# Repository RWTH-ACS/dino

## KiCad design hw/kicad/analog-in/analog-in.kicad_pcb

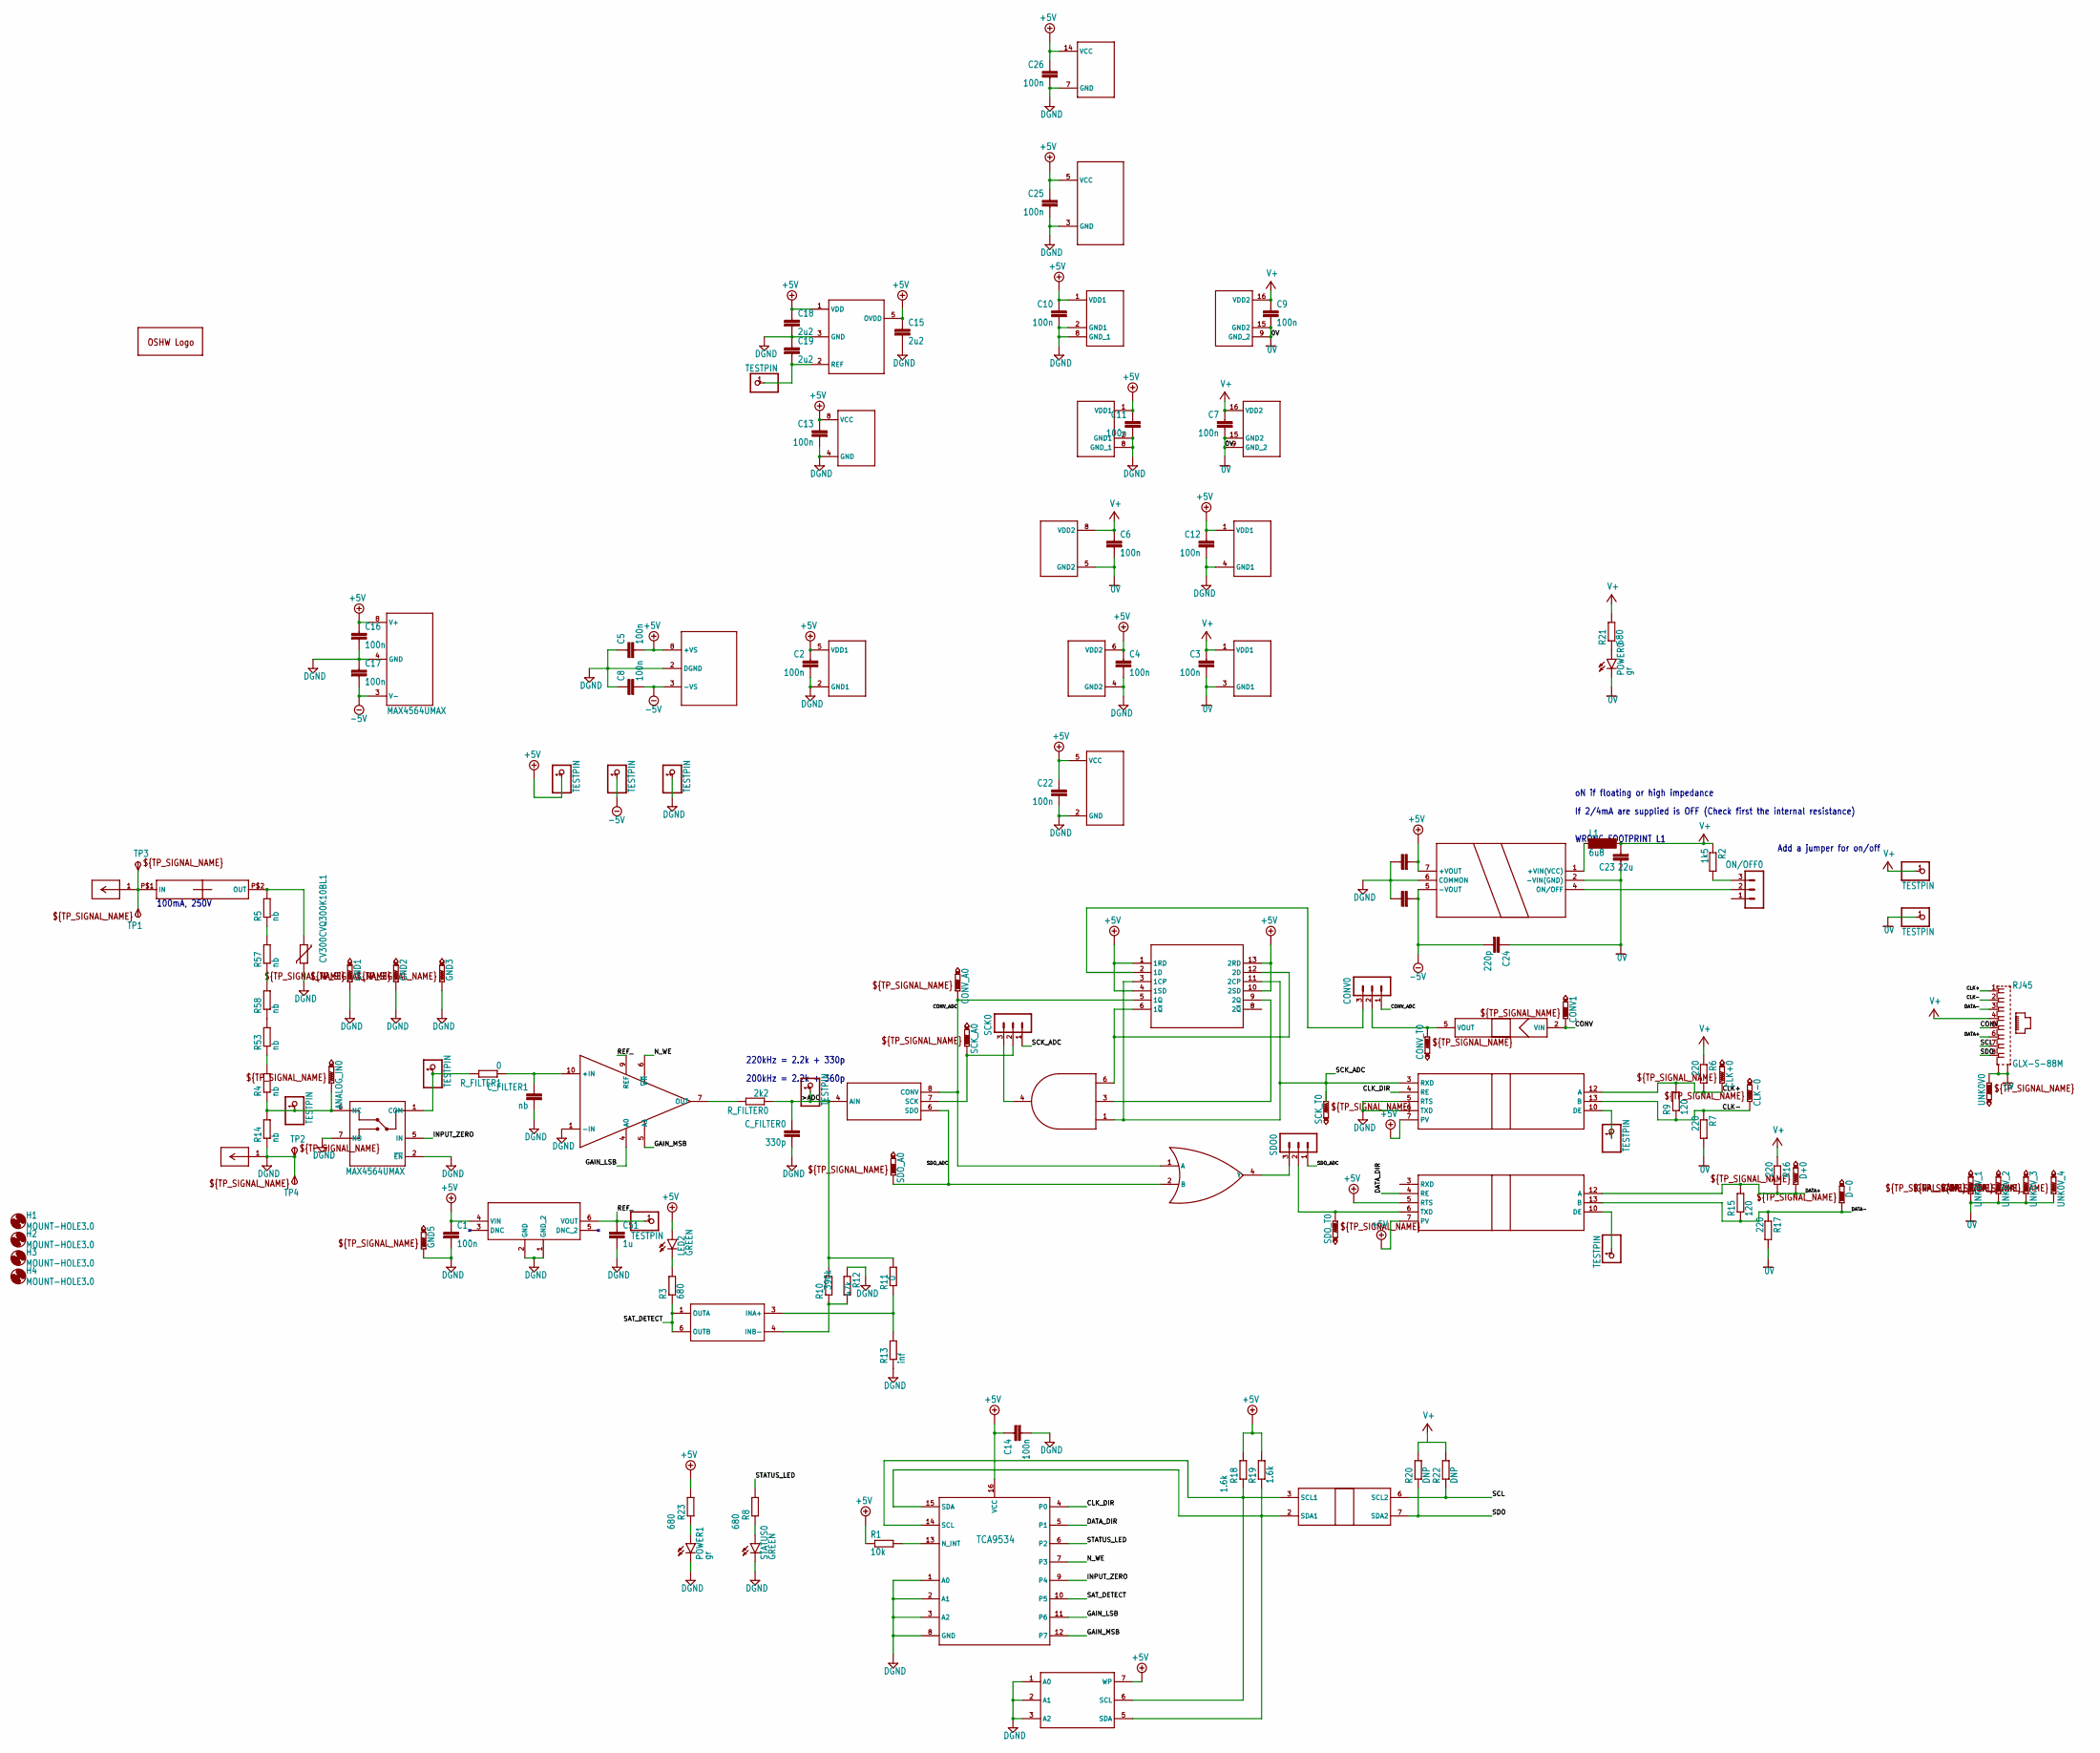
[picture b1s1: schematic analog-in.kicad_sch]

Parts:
+5V0: TESTPIN; 1X01
-5V0: TESTPIN; 1X01
ADC_0: LTC2314-14; TSOT-23_TS8_LIT; DIGIKEY LTC2314ITS8-14#TRMPBFT-ND
ADC_IN0: TESTPIN; 1X01
ADC_REF0: TESTPIN; 1X01
ANALOG_IN0: PTR1B1,27; B1,27
A_IN0: TESTPIN; 1X01
C1: 100n; C0805; DIGIKEY 478-7962-1-ND
C2, C3, C4, C5, C6, C7, C8, C9, C10, C11, C12, C13, C14, C16, C17, C20, C21, C22, C25, C26: 100n; C0805K; DIGIKEY 478-7962-1-ND
C15, C18, C19: 2u2; C0805K; DIGIKEY 1276-2954-2-ND
C23: 22u; C1206; DIGIKEY 399-17625-1-ND
C24: 220p; C1808; DIGIKEY 478-10448-2-ND
C51: 1u; C0805; DIGIKEY 1276-6471-1-ND
CLK+0: PTR1B1,27; B1,27
CLK-0: PTR1B1,27; B1,27
CONV0: MA03-1; DIGIKEY 732-5316-ND
CONV1: PTR1B1,27; B1,27
CONVERSION0: ADUM4120-1ARIZ; RI_6_1_ADI; DIGIKEY ADUM4120-1ARIZ-ND
CONV_A0: PTR1B1,27; B1,27
CONV_T0: PTR1B1,27; B1,27
C_FILTER0: 330p; C0805K; DIGIKEY 478-9885-1-ND
C_FILTER1: nb; C0805K; DIGIKEY 478-08055C121KAT2ACT-ND
D+0: PTR1B1,27; B1,27
D-0: PTR1B1,27; B1,27
DC-DC_CONVERTER0: TDN_3-1211WI; TDN3_TRP; MANUFACTURER_PART_NUMBER TDN 3-1221WISM; DIGIKEY TDN3-1221WISM-ND
DE_CLK0: TESTPIN; 1X01
DE_DATA0: TESTPIN; 1X01
DGND0: TESTPIN; 1X01
FILTER0: TESTPIN; 1X01
FLIP-FLOP0: 74HC74PW-Q100,118; TSSOP14_SOT402-1_NEX; DIGIKEY 1727-4083-1-ND
GND1, GND2, GND3, GND5: PTR1B1,27; B1,27
GND_4: TESTPIN; 1X01
GOLD_ORB_SM1: OSHWLOGOLOGO8MM; OSHW_8MM
H1, H2, H3, H4: MOUNT-HOLE3.0; 3,0
I2C0: ADUM1251WARZ; R_8_ADI; DIGIKEY ADUM1251ARZ-RL7TR-ND
INSTR_AMP0: AD8250ARMZ; RM_10_ADI; DIGIKEY AD8250ARMZ-R7TR-ND
L1: 6u8; SM-NE29; DIGIKEY 1951-1045-ND
LED2: GREEN; SML0805; DIGIKEY LTST-C170GKT
MINUS0: 23.3200-21; CONN_23.3200-21_SBI; DIGIKEY 501-73099-0-ND
MOV1: CV300CVQ300K10BL1; CVQ300K10
ON/OFF0: MA03-1; DIGIKEY 732-5316-ND
PLUS0: 23.3200-21; CONN_23.3200-21_SBI; DIGIKEY 501-73099-2-ND
POWER0, POWER1: gr; SML0805; DIGIKEY LTST-C170GKT
R1: 10k; R0805; DIGIKEY P10KDATR-ND
R2: 1k5; R0805; DIGIKEY P1.5KDATR-ND
R3, R21: 680; R0805; DIGIKEY A129747TR-ND
R4, R5, R53, R57, R58: nb; R1206; MOUSER check config
R6, R7, R16, R17: 220; R0805; DIGIKEY Y1624195R000Q9R-ND
R8, R23: 680; R0805
R9, R15: 120; R0805; DIGIKEY Y1629-120DTR-ND
R10: 390k; R0805; DIGIKEY 2019-RK73H2ATTD3903FTR-ND
R11: 0; R0805; DIGIKEY RMCF0805ZT0R00TR-ND
R12: 47k; R0805; DIGIKEY A130144TR-ND
R13: inf; R0805
R14: nb; R0805; MOUSER check config
R18, R19: 1.6k; R0805
R20, R22: DNP; R0805
REF0: LT6654AIS6-2.048TRMPBF; S_6_ADI; DIGIKEY 161-LT6654BHS6-2.048#WTRPBFTR-ND
REF_2.048: TESTPIN; 1X01
RJ45: GLX-S-88M; DIGIKEY 2092-GLX-S-88M-ND
ROHM_I2C0: BR24T1MF-3AM; BR24T1MFJ-3AM; DIGIKEY BR24T1MF-3AME2TR-ND
R_FILTER0: 2k2; R0805; DIGIKEY A106060TR-ND
R_FILTER1: 0; R0805; DIGIKEY P220DACT-ND
SATURATION_DETECT0: ADCMP670-1YUJZ-RL7; UJ_6_ADI; DIGIKEY ADCMP670-1YUJZ-RL7TR-ND
SCK0: MA03-1; DIGIKEY 732-5316-ND
SCK_A0: PTR1B1,27; B1,27
SCK_T0: PTR1B1,27; B1,27
SDO0: MA03-1; DIGIKEY 732-5316-ND
SDO_A0: PTR1B1,27; B1,27
SDO_T0: PTR1B1,27; B1,27
SERIAL_CLOCK0: ADM2486BRWZ-REEL; RW_16_ADI; DIGIKEY ADM2486BRWZ-REELTR-ND
SERIAL_DATA0: ADM2486BRWZ-REEL; RW_16_ADI; DIGIKEY ADM2486BRWZ-REELTR-ND
SN74LVC1G32: SN74LVC1G32DCKTDCK5-M; DCK5-M
STATUS0: GREEN; CHIPLED_0805; DIGIKEY LTST-C170GKT
TP1, TP2, TP3, TP4: TPSTP20SQ; TP20SQ
U$1: 0508.500MXEP; DIGIKEY 283-4458-1-ND
U$2: TCA9534; TSSOP16L
U$20: MAX4564UMAX; UMAX8; DIGIKEY MAX4564EUA+TR-ND
UNK0V0, UNK0V_1, UNK0V_2, UNK0V_3, UNK0V_4: PTR1B1,27; B1,27
UNK74LVC1G11: SN74LVC1G11DBVRDBV0006A_L; DBV0006A_L
VCC0: TESTPIN; 1X01

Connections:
0V: C3.2, C6.2, C7.2, C9.2, C23.1, C24.1, CONVERSION0.3 (GND1), DC-DC_CONVERTER0.2 (-VIN(GND)), DGND0.1, I2C0.5 (GND2), POWER0.C, R7.2, R17.2, RJ45.S1, RJ45.S2, SERIAL_CLOCK0.9 (GND_2), SERIAL_CLOCK0.15 (GND2), SERIAL_DATA0.9 (GND_2), SERIAL_DATA0.15 (GND2), UNK0V0.TP, UNK0V_1.TP, UNK0V_2.TP, UNK0V_3.TP, UNK0V_4.TP
+5V: +5V0.1, ADC_0.1 (VDD), ADC_0.5 (OVDD), C1.1, C2.1, C4.1, C5.2, C10.1, C11.1, C12.1, C13.1, C14.1, C15.1, C16.1, C18.1, C20.2, C22.1, C25.1, C26.1, CONVERSION0.6 (VDD2), DC-DC_CONVERTER0.7 (+VOUT), FLIP-FLOP0.1 (1RD), FLIP-FLOP0.4 (1SD), FLIP-FLOP0.10 (2SD), FLIP-FLOP0.13 (2RD), FLIP-FLOP0.14 (VCC), I2C0.1 (VDD1), INSTR_AMP0.8 (+VS), LED2.A, R1.1, R18.2, R19.2, R23.2, REF0.4 (VIN), ROHM_I2C0.7 (WP), ROHM_I2C0.8 (VCC), SATURATION_DETECT0.5 (VDD1), SERIAL_CLOCK0.1 (VDD1), SERIAL_CLOCK0.7 (PV), SERIAL_DATA0.1 (VDD1), SERIAL_DATA0.5 (RTS), SERIAL_DATA0.7 (PV), SN74LVC1G32.5 (VCC), U$2.16 (VCC), U$20.8 (V+), UNK74LVC1G11.5 (VCC)
-5V: -5V0.1, C8.2, C17.2, C21.2, C24.2, DC-DC_CONVERTER0.5 (-VOUT), INSTR_AMP0.3 (-VS), U$20.3 (V-)
>ADC: ADC_0.4 (AIN), ADC_IN0.1, C_FILTER0.1, R10.2, R11.2, R_FILTER0.1
CLK+: CLK+0.TP, R6.2, R9.2, RJ45.1, SERIAL_CLOCK0.12 (A)
CLK-: CLK-0.TP, R7.1, R9.1, RJ45.2, SERIAL_CLOCK0.13 (B)
CLK_DIR: SERIAL_CLOCK0.4 (RE), U$2.4 (P0)
CONV: CONV1.TP, CONVERSION0.2 (VIN), RJ45.5
CONV_ADC: ADC_0.8 (CONV), CONV0.1, CONV_A0.TP, FLIP-FLOP0.5 (1Q), SN74LVC1G32.1 (A)
DATA+: D+0.TP, R15.2, R16.2, RJ45.6, SERIAL_DATA0.12 (A)
DATA-: D-0.TP, R15.1, R17.1, RJ45.3, SERIAL_DATA0.13 (B)
DATA_DIR: SERIAL_DATA0.4 (RE), U$2.5 (P1)
DGND: ADC_0.3 (GND), C1.2, C2.2, C4.2, C5.1, C8.1, C10.2, C11.2, C12.2, C13.2, C14.2, C15.2, C16.2, C17.1, C18.2, C19.1, C20.1, C21.1, C22.2, C25.2, C26.2, C51.2, CONVERSION0.4 (GND2), C_FILTER0.2, C_FILTER1.2, DC-DC_CONVERTER0.6 (COMMON), FLIP-FLOP0.7 (GND), GND1.TP, GND2.TP, GND3.TP, GND5.TP, GND_4.1, I2C0.4 (GND1), INSTR_AMP0.1 (-IN), INSTR_AMP0.2 (DGND), MINUS0.1, MOV1.2, POWER1.C, R12.1, R13.1, R14.1, REF0.1 (GND_2), REF0.2 (GND), ROHM_I2C0.1 (A0), ROHM_I2C0.2 (A1), ROHM_I2C0.3 (A2), ROHM_I2C0.4 (GND), SATURATION_DETECT0.2 (GND1), SERIAL_CLOCK0.2 (GND1), SERIAL_CLOCK0.5 (RTS), SERIAL_CLOCK0.6 (TXD), SERIAL_CLOCK0.8 (GND_1), SERIAL_DATA0.2 (GND1), SERIAL_DATA0.8 (GND_1), SN74LVC1G32.3 (GND), STATUS0.C, TP2.TP, TP4.TP, U$2.1 (A0), U$2.2 (A1), U$2.3 (A2), U$2.8 (GND), U$20.2 (~EN), U$20.4 (GND), U$20.7 (NO), UNK74LVC1G11.2 (GND)
GAIN_LSB: INSTR_AMP0.4 (A0), U$2.11 (P6)
GAIN_MSB: INSTR_AMP0.5 (A1), U$2.12 (P7)
INPUT_ZERO: U$2.9 (P4), U$20.5 (IN)
unnamed: INSTR_AMP0.7 (OUT), R_FILTER0.2
unnamed: R1.2, U$2.13 (N_INT)
unnamed: DE_CLK0.1, SERIAL_CLOCK0.10 (DE)
unnamed: I2C0.3 (SCL1), R18.1, ROHM_I2C0.6 (SCL), U$2.14 (SCL)
unnamed: FILTER0.1, R_FILTER1.2, U$20.1 (COM)
unnamed: I2C0.2 (SDA1), R19.1, ROHM_I2C0.5 (SDA), U$2.15 (SDA)
unnamed: DE_DATA0.1, SERIAL_DATA0.10 (DE)
unnamed: ADC_0.2 (REF), ADC_REF0.1, C19.2
unnamed: MOV1.1, R5.2, U$1.P$2 (OUT)
unnamed: DC-DC_CONVERTER0.1 (+VIN(VCC)), L1.1
unnamed: ON/OFF0.3, R2.2
unnamed: DC-DC_CONVERTER0.4 (ON/OFF), ON/OFF0.2
unnamed: SCK0.3, UNK74LVC1G11.4 (Y)
unnamed: LED2.C, R3.2
unnamed: C_FILTER1.1, INSTR_AMP0.10 (+IN), R_FILTER1.1
unnamed: PLUS0.1, TP1.TP, TP3.TP, U$1.P$1 (IN)
unnamed: R10.1, R12.2, SATURATION_DETECT0.4 (INB-)
unnamed: R11.1, R13.2, SATURATION_DETECT0.3 (INA+)
unnamed: FLIP-FLOP0.6 (1~Q), FLIP-FLOP0.12 (2D), UNK74LVC1G11.6 (C)
unnamed: ANALOG_IN0.TP, A_IN0.1, R4.1, R14.2, U$20.6 (NC)
unnamed: R57.1, R58.2
unnamed: R8.1, STATUS0.A
unnamed: FLIP-FLOP0.9 (2Q), UNK74LVC1G11.3 (B)
unnamed: CONV0.2, CONVERSION0.5 (VOUT), CONV_T0.TP
unnamed: CONV0.3, FLIP-FLOP0.2 (1D)
unnamed: ADC_0.7 (SCK), SCK0.2, SCK_A0.TP
unnamed: POWER1.A, R23.1
unnamed: R4.2, R53.1
unnamed: SDO0.2, SDO_T0.TP, SERIAL_DATA0.6 (TXD)
unnamed: SDO0.3, SN74LVC1G32.4 (Y)
unnamed: POWER0.A, R21.1
unnamed: R53.2, R58.1
unnamed: R5.1, R57.2
N_WE: INSTR_AMP0.6 (~WR), U$2.7 (P3)
REF_: C51.1, INSTR_AMP0.9 (REF), REF0.6 (VOUT), REF_2.048.1
SAT_DETECT: R3.1, SATURATION_DETECT0.1 (OUTA), SATURATION_DETECT0.6 (OUTB), U$2.10 (P5)
SCK_ADC: FLIP-FLOP0.3 (1CP), FLIP-FLOP0.11 (2CP), SCK0.1, SCK_T0.TP, SERIAL_CLOCK0.3 (RXD), UNK74LVC1G11.1 (A)
SCL: I2C0.6 (SCL2), R22.1, RJ45.7
SDO: I2C0.7 (SDA2), R20.1, RJ45.8
SDO_ADC: ADC_0.6 (SDO), SDO0.1, SDO_A0.TP, SN74LVC1G32.2 (B)
STATUS_LED: R8.2, U$2.6 (P2)
V+: C3.1, C6.1, C7.1, C9.1, C23.2, CONVERSION0.1 (VDD1), I2C0.8 (VDD2), L1.2, R2.1, R6.1, R16.1, R20.2, R21.2, R22.2, RJ45.4, SERIAL_CLOCK0.16 (VDD2), SERIAL_DATA0.16 (VDD2), VCC0.1

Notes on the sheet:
220kHz = 2.2k + 330p
WRONG FOOTPRINT L1
If 2/4mA are supplied is OFF (Check first the internal resistance)
Add a jumper for on/off
100mA, 250V
oN if floating or high impedance
200kHz = 2.2k + 360p

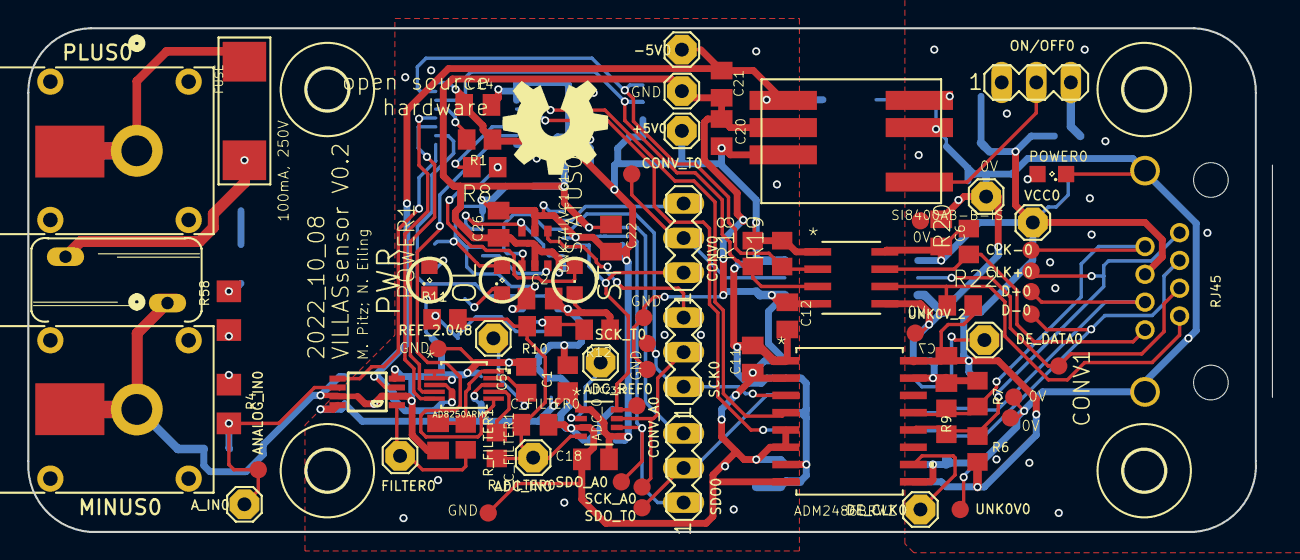
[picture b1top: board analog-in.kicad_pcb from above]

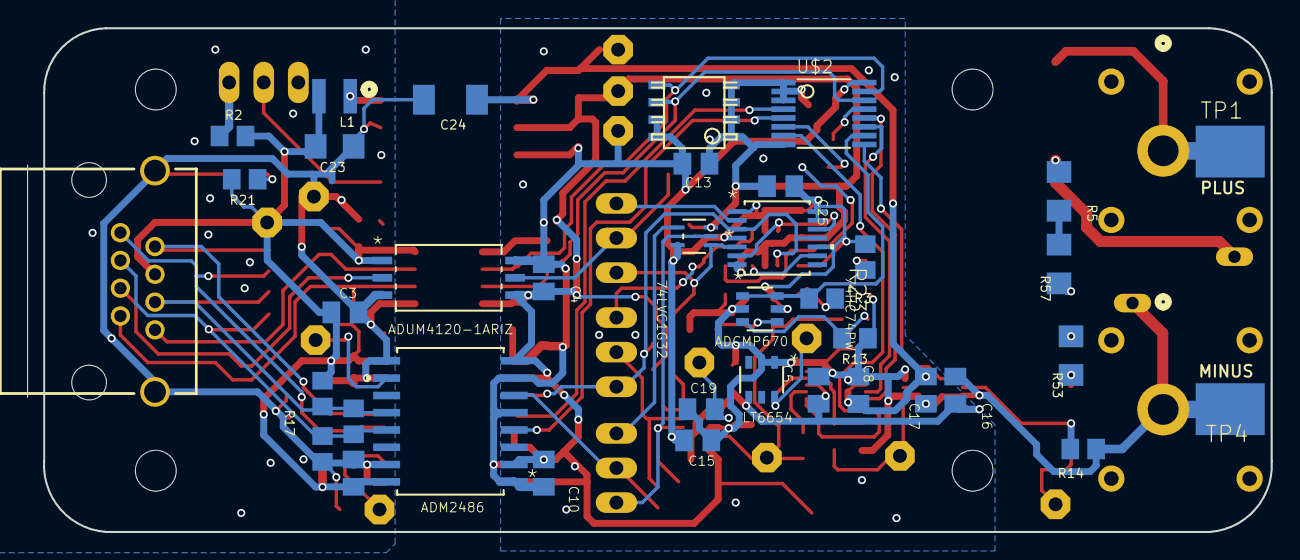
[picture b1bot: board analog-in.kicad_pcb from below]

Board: 2 copper layers, 91.3 x 37.0 mm, 128 parts (37 on the bottom side), 58 nets.

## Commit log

2021-11-26 add license, readme and gitignore
2021-11-26 add analog-in pcb
2021-11-26 initial commit. Adding analog in hardware, corresponding software and fpga design, draft for fmc hardware, etc.
2021-11-26 fpga-fmc: add LPC pin assignment of FMC connector
2021-11-26 fpga-fmc: fix board layout
2021-11-26 fpga-fmc: add devices from analog-in pcb
2021-11-26 fpga-fmc: add more isolator ics. add i2c switch ic
2021-11-26 fpga-fmc: add 4 channel isolator ic
2021-12-03 analog-in: add comments with PCB mistakes
2021-12-03 sw/arduino: add i2c functions, verify i2c functionality, read saturation check
2021-12-03 sw/arduino: add error compensation
2021-12-10 hw/analog-in: add mistake comment
2021-12-10 hw/fpga-fmc: add and route rs485 transceiver for 3 channels
2021-12-10 sw/arduino/analog-in: work on arduino test sw
2021-12-13 fpga-fmc: add i2c circuit and level shifter for conv signal
2021-12-14 fpga_fmc: route conv signals and more rj channels
2021-12-15 fpga-fmc: route right side
2022-01-06 hw/fpga-fmc: add 5V supply and route remaining CONV signals
2022-02-17 arduino/analog-in: make arduino led blink, improve comments
2022-05-02 hw/fpga-fmc: finalize pcb design and prepare BOM
2022-05-03 hw/fpga-fmc: fix clearance issues
2022-06-01 hw/fpga-fmc: add documentation and code to program fmc eeprom
2022-06-01 hw/fpga-fmc: add cross compile steps
2022-06-07 hdl: create constraints for dino fpga interface. Modify IP for hardware verification
2022-06-07 hw/fpga-fmc: fix connector turned by 180 degrees. add led for 1v8. change i2c package
2022-06-07 sw/arduino/analog-in: work on arduino sw
2022-06-07 hdl: copy all pin assignments to constraint file
    note: RJ8 FMC connection are not connected on the FPGA board, so RJ8 cannot be used with the prototype pcb
2022-08-02 turn FMC connector and reroute signals
2022-08-04 hw/fpga-fmc: rewire pin header and screw terminal.
2022-08-08 hw/fpga-fmc: reposition i2c switch
2022-08-25 hw/fpga-fmc: optimize routing
2022-08-25 sw/arduino/analog-in: improve error output
2022-08-25 hdl/vivado: update constraints to deactivate wrongly routed channels
2022-08-25 hdl/vivado: update block design to deactivate non-working channels
2022-08-26 hw/analog-in: fix mistakes from rev 1
2022-08-26 hw/fmc minor cleanup in layout and schematic
2022-08-26 hw/fpga-fmc: align GND vias
2022-08-29 hw/fpga-fmc: make rs485 termination resistors 0805 for better power rating
2022-09-08 fpga-fmc: last fixes before production of rev B
2022-09-08 hw: add analog-out as copy of analog-in
2022-09-08 ADC board fixes
2022-09-12 hw/analog-out: add part nr for isolator
2022-09-13 hw/fpga-fmc: fix wrong connection on bottom row rj-45 connectors
2022-09-19 hw/fpga-fmc: fix more issues on adapter board
2022-09-19 hdl/vivado: change for rev B PCB
2022-11-03 hdl/vivado: update vivado design
2022-11-03 hw/analog-in: update schematics for analog in
2022-11-03 hw/fpga-fmc/eeprom: add Makefile
2022-11-03 hw/fpga-fmc: make i2c bus id configurable in fmceeprom_write.c
2022-11-03 hw/fpga-fmc/eeprom: use 2to3 to convert fru-generator ot python3
2022-11-03 hw/fpga-fmc/eeprom: install python script to bin/fmc
2022-11-03 hw/fpga-fmc/eeprom: fix makefile installing to wrong path
2022-11-03 First verision of dac schematic
2022-11-03 hw/fpga-fmc/eeprom: fix wrong arg number check
2022-11-18 hdl: add scale and offset and aurora ips to forward dino data to aurora link
2022-11-18 hw/fpga-fmc: update eagle project file
2022-11-18 hdl: add append_seqnum IP and testbench
2022-11-28 hdl: add append seqnum that adds signals to fill up message to a certain size
2022-11-28 hdl: add dinoif_fast_tb that simulates the dino ADC, edge injection logic and delay lines
2022-11-28 hdl: verify and fix dinoif_fast
2022-11-28 hdl: integrate new dinoif_fast into block design
2022-12-12 hdl/vivado: add i2c IP to design
2022-12-12 hw/analog-in: add note
2023-08-14 first revision of dac board
2023-08-14 add polygon
2023-10-13 updated version of board and schematic
2023-10-16 hw: change isolator to si8400ab
2023-10-16 hw: fix part numbers
2023-10-23 hdl: add dac and fix adc IP
2023-10-25 hdl: update board design
2023-12-05 sw/dino-config: add code to configure dino via i2c from SoC
2023-12-05 sw/dino-config: add eeprom reading and writing
2024-04-16 move eagle
2024-04-16 add kicad
2024-04-16 update adc to latest version
2024-04-16 update readme and gitignore
2024-04-16 cleanup
2024-04-18 hdl: fix design to work with LTC2314 ADC
2024-04-26 hw: move eeprom program back to original location
2024-06-18 hdl: make config timer accept new timer value synchronous to separate clock
2024-06-18 hdl: remove GTH LOC constraint
2024-09-25 hdl: add prepend_seqnumg IP
2025-01-24 update vivado files
